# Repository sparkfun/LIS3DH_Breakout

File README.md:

SparkFun Triple Axis Accelerometer Breakout - LIS3DH
=============================================

[*SparkFun Triple Axis Accelerometer Breakout - LIS3DH(SEN-XXXXX)*](https://www.sparkfun.com/products/XXXXX)

This breakout board makes it easy to use the tiny LIS3DH accelerometer in your project. 
The LIS3DH is a smart low-power, three-axis, capacitive micro-machined accelerometer with 12 bits of resolution.

This product replaced the MMA-8452Q.

Repository Contents
-------------------
* **/Hardware** - All Eagle design files (.brd, .sch)
* **/Production** - Production panel files (.brd)

Documentation
--------------
* **[Library](GitHub library URL)** - <LANGUAGE> library for the <PRODUCT NAME>.
* **[Hookup Guide](Learn.SparkFun URL)** - Basic hookup guide for the <PRODUCT NAME>.
* **[SparkFun Fritzing repo](https://github.com/sparkfun/Fritzing_Parts)** - Fritzing diagrams for SparkFun products.
* **[SparkFun 3D Model repo](https://github.com/sparkfun/3D_Models)** - 3D models of SparkFun products. 
* **[SparkFun Graphical Datasheets](https://github.com/sparkfun/Graphical_Datasheets)** -Graphical Datasheets for various SparkFun products.

Product Versions
----------------
* [Part SKU](part URL)- Basic part and short description here
* [Retail part SKU] (retail URL)- Retail packaging of standard description here
* [Any other parts this repo covers](any other URLs) - Description of said parts

Version History
---------------
* [V_0.1](https://github.com/sparkfun/LIS3DH_Breakout/tree/V_0.1) - Prototype
* [V_1.0](https://github.com/sparkfun/LIS3DH_Breakout/tree/V_1.0) - Release Version

License Information
-------------------

This product is _**open source**_! 

Please review the LICENSE.md file for license information. 

If you have any questions or concerns on licensing, please contact techsupport@sparkfun.com.

Distributed as-is; no warranty is given.

- Your friends at SparkFun.

_<COLLABORATION CREDIT>_

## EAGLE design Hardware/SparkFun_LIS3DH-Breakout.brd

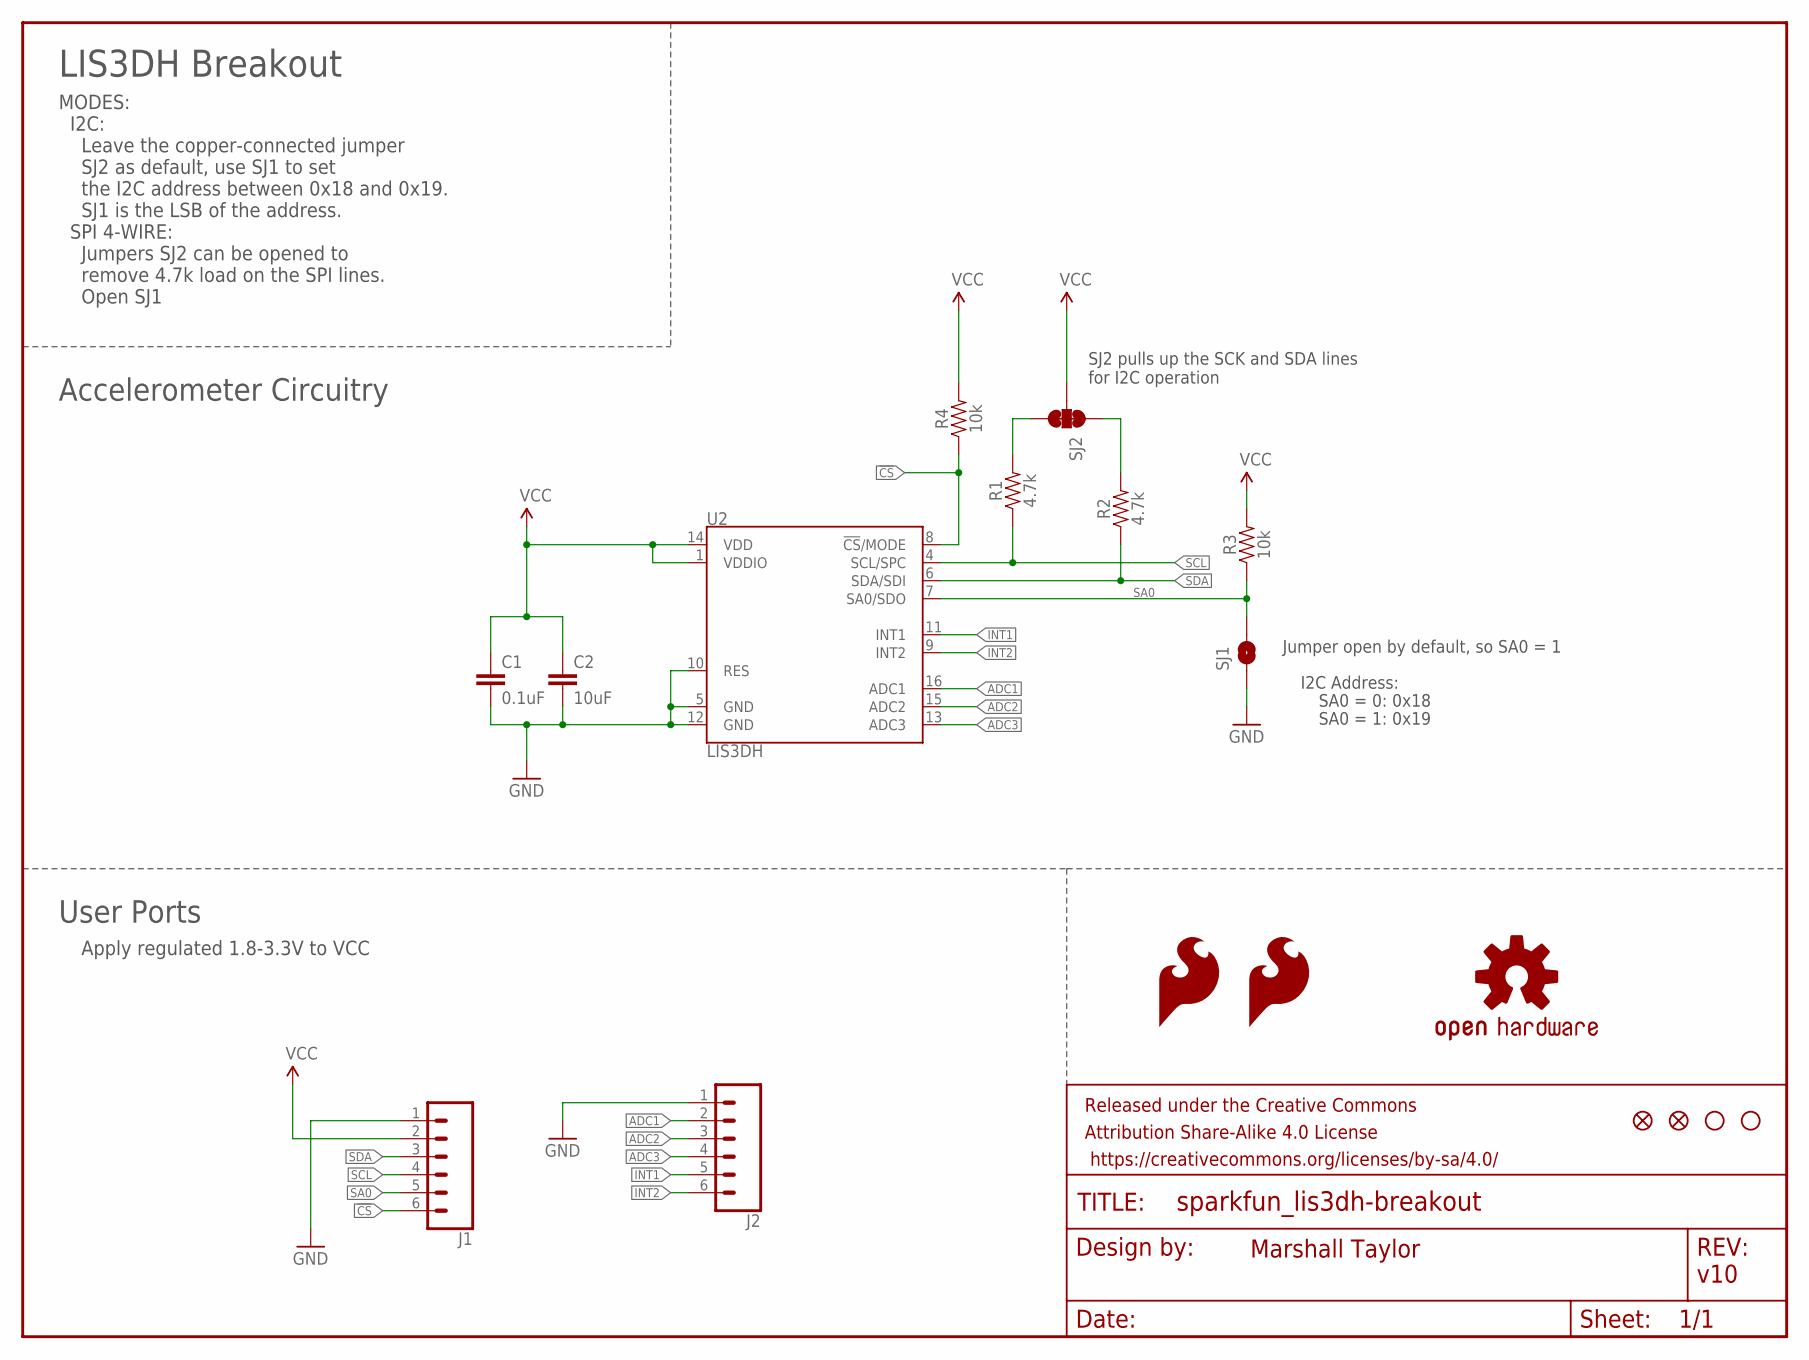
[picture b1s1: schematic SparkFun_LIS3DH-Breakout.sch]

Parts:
C1: 0.1uF; 0402
C2: 10uF; 0603
FRAME2: FRAME-LETTER; CREATIVE_COMMONS
J1, J2: CONN_06NO_SILK_FEMALE_PTH; 1X06_NO_SILK
JP2, JP6: FIDUCIALUFIDUCIAL; MICRO-FIDUCIAL
JP3, JP4: STAND-OFF
LOGO1, LOGO2: SFE_LOGO_FLAME.1_INCH; SFE_LOGO_FLAME_.1
R1, R2: 4.7k; 0603
R3, R4: 10k; 0603
SJ1: SOLDERJUMPERNO; SJ_2S-NO
SJ2: JUMPER-PAD-3-NC_BY_TRACE; PAD-JUMPER-3-3OF3_NC_BY_TRACE_YES_SILK_FULL_BOX
U2: LIS3DH; LGA-16-3X3
U$1: OSHW-LOGOS; OSHW-LOGO-S

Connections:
!CS: J1.6, R4.1, U2.8 (!CS!/MODE)
ADC1: J2.2, U2.16 (ADC1)
ADC2: J2.3, U2.15 (ADC2)
ADC3: J2.4, U2.13 (ADC3)
GND: C1.2, C2.2, J1.1, J2.1, SJ1.1, U2.5 (GND), U2.10 (RES), U2.12 (GND)
INT1: J2.5, U2.11 (INT1)
INT2: J2.6, U2.9 (INT2)
unnamed: R2.2, SJ2.1
unnamed: R1.2, SJ2.3
SA0: J1.5, R3.1, SJ1.2, U2.7 (SA0/SDO)
SCL: J1.4, R1.1, U2.4 (SCL/SPC)
SDA: J1.3, R2.1, U2.6 (SDA/SDI)
VCC: C1.1, C2.1, J1.2, R3.2, R4.2, SJ2.2, U2.1 (VDDIO), U2.14 (VDD)

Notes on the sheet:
I2C Address:
SA0 = 0: 0x18
SA0 = 1: 0x19
Jumper open by default, so SA0 = 1
v10
Marshall Taylor
LIS3DH Breakout
SJ2 pulls up the SCK and SDA lines for I2C operation
MODES: I2C: Leave the copper-connected jumper SJ2 as default, use SJ1 to set the I2C address between 0x18 and 0x19. SJ1 is the LSB of the address. SPI 4-WIRE: Jumpers SJ2 can be opened to remove 4.7k load on the SPI lines. Open SJ1
Accelerometer Circuitry
User Ports
Apply regulated 1.8-3.3V to VCC

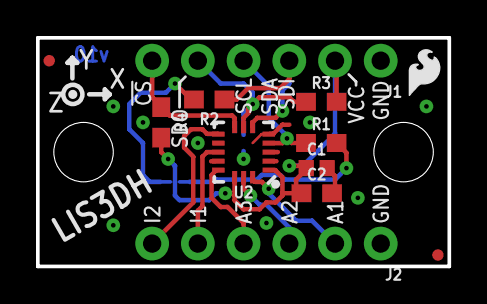
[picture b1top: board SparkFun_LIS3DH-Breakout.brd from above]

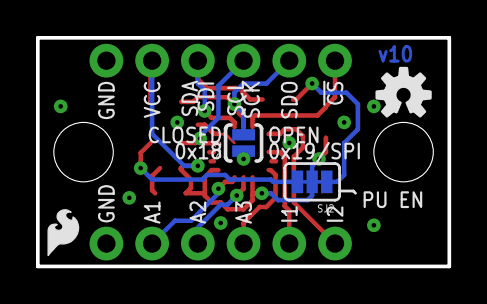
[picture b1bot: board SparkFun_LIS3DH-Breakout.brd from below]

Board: 2 copper layers, 22.9 x 12.7 mm, 19 parts (4 on the bottom side), 13 nets.

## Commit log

2016-06-03 Initial commit - Hardware copied from MMA-8452Q repo
2016-06-07 Implanted LIS3DH into previous design, renamed files but basically the design is still really the old design with the new IC. This is a turning point before adding more features. Also, the gitignore 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
2016-06-07 Finished design for proto 1
2016-06-09 Updated design based off design review
2016-06-09 Adjusted a trace and updated components to most recent libraries
2016-06-09 fixed airwire and renamed C3 to C2
2016-08-17 Fixed silk: added address/jumper function, pumped up the product name silk. Swapped I1 and I2. Added more topside labeling
2016-08-17 removed 'ADR' and : silks
2016-08-18 Applied review changes
2017-01-03 updating readme with new product links
2017-01-03 Squashed 'Libraries/Arduino/' content from commit 7dddbcc
    git-subtree-dir: Libraries/Arduino
    git-subtree-split: 7dddbcca47f75477a0a8c26ba2455d239bf04937

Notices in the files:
parts and their libraries:
SparkFun-Sensors: Licensing: Creative Commons ShareAlike 4.0 International - https://creativecommons.org/licenses/by-sa/4.0
SparkFun-Aesthetics: Released under the Creative Commons Attribution Share-Alike 4.0 License
SparkFun-Aesthetics: https://creativecommons.org/licenses/by-sa/4.0
